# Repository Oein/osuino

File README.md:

# osuino

OSU mania implementation in arduino.

Currently making in web with wasm, to build and test much faster than testing on real arduino.

# TODO

 - [X] Intro
 - [X] Title menu
 - [ ] Select menu
   - [X] Select menu UI
   - [X] Selet menu load from FS
   - [ ] Selet menu load from SD Card
 - [X] Ingame
   > Now has an arduino crash beacuse of running out of ram
 - [ ] Results
 - [ ] Map downloads
 - [ ] Settings
   - [ ] WIFI Config
   - [ ] Note speed
   - [ ] Maybe bluetooth audio supporting?
 - [X] Input Kerboard
 - [X] Read osu map file
 - [X] API for arduino

# Screenshots

| img1 | img2 | img3 |
|:--:|:--:|:--:|
|  |  |  |

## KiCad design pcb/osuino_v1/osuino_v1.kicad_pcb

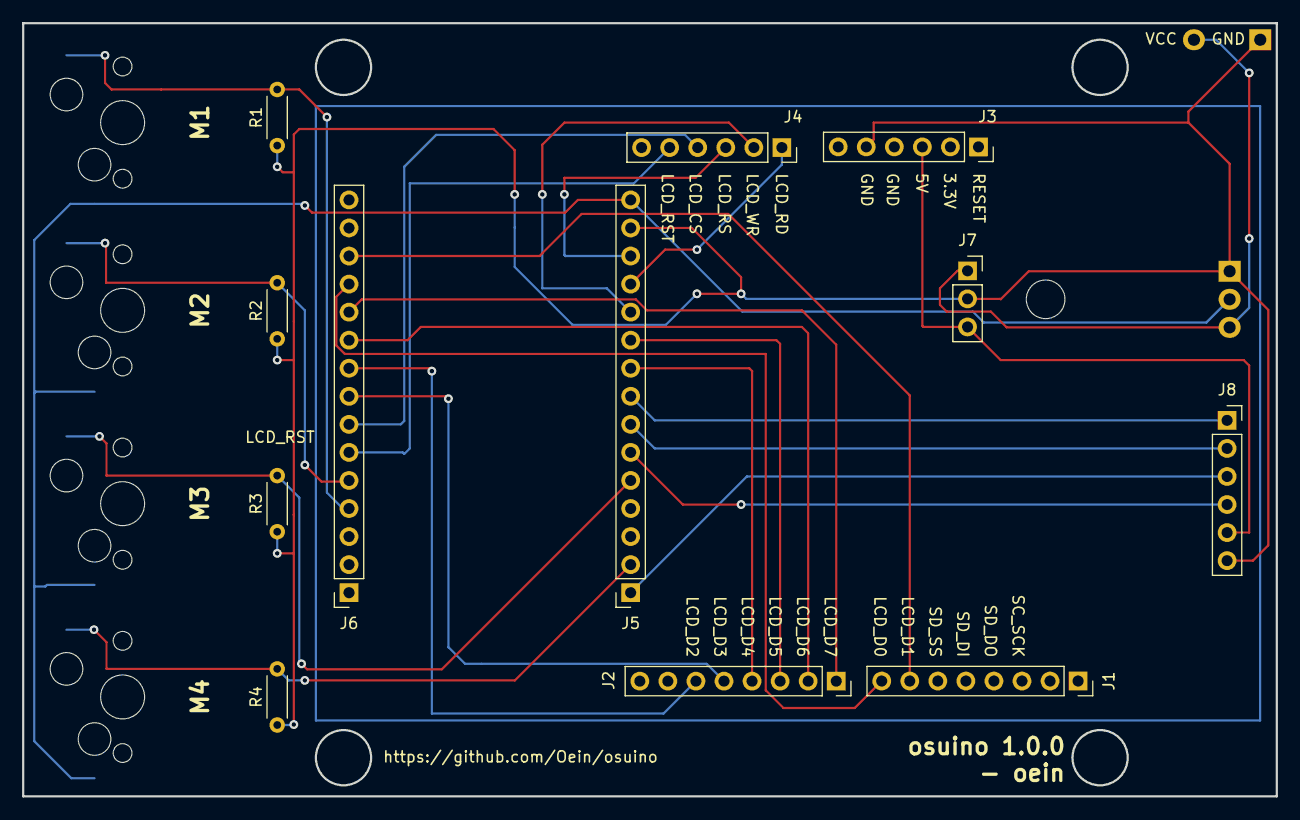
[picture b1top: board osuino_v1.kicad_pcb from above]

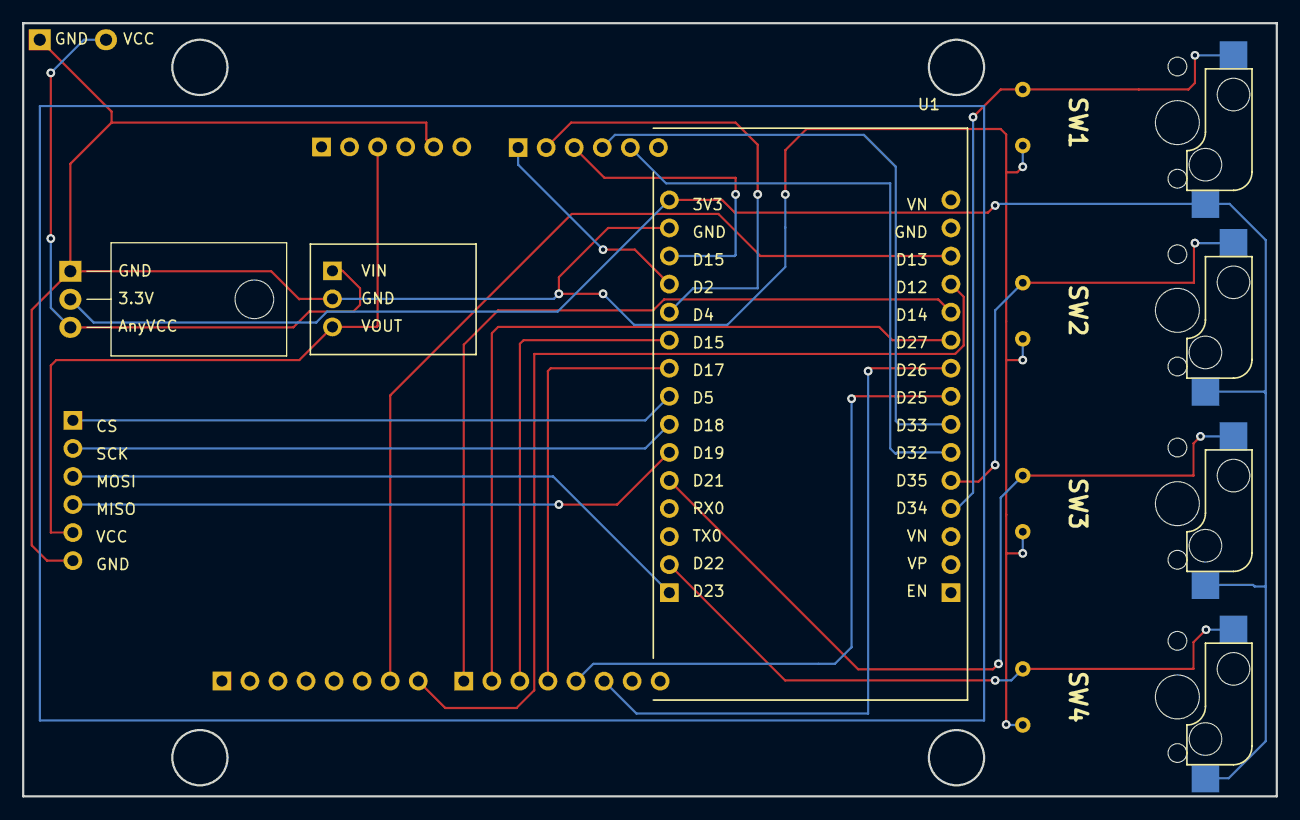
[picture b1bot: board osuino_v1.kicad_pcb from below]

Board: 2 copper layers, 113.5 x 70.0 mm, 17 parts (5 on the bottom side), 25 nets.

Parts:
J1, J2: Conn_01x08_Socket; PinSocket_1x08_P2.54mm_Vertical
J3, J4, J8: Conn_01x06_Socket; PinSocket_1x06_P2.54mm_Vertical
J5, J6: Conn_01x15_Socket; PinSocket_1x15_P2.54mm_Vertical
J7: Conn_01x03_Socket; PinSocket_1x03_P2.54mm_Vertical
R1, R2, R3, R4: R; R_Axial_DIN0204_L3.6mm_D1.6mm_P5.08mm_Horizontal
SW1: M1; Kailh_MX_Socket
SW2: M2; Kailh_MX_Socket
SW3: M3; Kailh_MX_Socket
SW4: M4; Kailh_MX_Socket
U1: LM1117T-3.3(DIP); TO-220-3_Horizontal_TabDown

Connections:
GND: J3.5, J5.14, J7.2, J8.6, R1.1, R2.1, R3.1, R4.1, U1.1 (GND)
unnamed: J1.7, J6.13
unnamed: J1.8, J6.12
unnamed: J2.1, J6.11
unnamed: J2.2, J6.10
unnamed: J2.3, J5.10
unnamed: J2.4, J5.9
unnamed: J2.5, J6.8
unnamed: J2.6, J6.9
unnamed: J3.3, J7.3, J8.5
unnamed: J4.1, J5.12
unnamed: J4.2, J5.11
unnamed: J4.3, J5.13
unnamed: J4.4, J6.7
unnamed: J4.5, J6.6
unnamed: J5.1, J8.3
unnamed: J5.2, R4.2, SW4.2
unnamed: J5.5, R3.2, SW3.2
unnamed: J5.6, J8.4
unnamed: J5.7, J8.2
unnamed: J5.8, J8.1
unnamed: J5.15, U1.2 (VO)
unnamed: J6.4, R1.2, SW1.2
unnamed: J6.5, R2.2, SW2.2
VCC: J7.1, SW1.1, SW2.1, SW3.1, SW4.1, U1.3 (VI)

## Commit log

2025-02-17 color optimize
2025-02-17 add readme
2025-02-17 edit
2025-02-17 add build script
2025-02-18 add electron
2025-02-18 ingame
2025-02-19 arduino
2025-02-19 remove source
2025-02-19 serial key
2025-02-19 add no animate
2025-02-19 text fix
2025-02-19 mid commit
2025-02-19 arduino optimize
2025-02-19 wasm thing
2025-02-19 almost done made
2025-02-19 memory limit
2025-02-20 sofar
2025-02-22 code so far
2025-02-27 rename
2025-03-01 env template
2025-03-07 fix display resetting
2025-03-26 hardware v1
2025-03-26 use real button
2025-03-26 add util
2025-03-26 ignore map files
